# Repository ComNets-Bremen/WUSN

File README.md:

# MoleNet: A Wireless Underground Sensor Network Platform

**MoleNet** is a versatile Wireless Underground Sensor Network (WUSN) platform designed for education and low-power environmental monitoring.
This repository contains all relevant resources, including PCB layouts, source code, and examples to test and evaluate the platform.

Further information can be found on the official [MoleNet Website](https://molenet.org/)!

> ⚠️ **Note:** This is an active project. The files and directory structure are subject to change.

## New ESP32-based MoleNet!

After a long journey, we are finally at a point where we are testing the current version on a larger scale.
The latest version of MoleNet features several key improvements:

- **ESP32-S3 microcontroller**: A powerful yet energy-efficient processor that supports various development ecosystems including [MicroPython](https://micropython.org/), [Arduino](https://www.arduino.cc/), and [RiotOS](https://www.riot-os.org/)
- **SDI-12 sensor interface**: Compatible with high-quality environmental sensors
- **Micro-SD card support**: Enables extensive local data storage
- **SX1276-based LoRa transceiver**: Provides long-range wireless communication
- **On-board BME280 sensor**: Measures temperature, barometric pressure, and humidity [BME280](https://www.bosch-sensortec.com/products/environmental-sensors/humidity-sensors-bme280/)
- **Low-power design**: Ensures long battery life for extended deployments
- **qwiic connectivity**: Simplifies integration of I2C-based sensors, as, for
  example, available here: [Sparkfun](https://www.sparkfun.com/qwiic)

## Older Versions

Documentation for the ATMEGA-based MoleNet boards can be found in the [documentation directory](docs/MoleNet_ATMEGA.md).

## Changelog

The list of changes and the evolution of MoleNet is listed in the
[changelog](CHANGELOG.md).

## Publications

The following list gives some MoleNet-related publications:

- Gellhaar, M., Dede, J., Koehler, H., & Förster, A. (2016, February). Design and Evaluation of Underground Wireless Sensor Networks for Reforestation Monitoring. [In EWSN (pp. 229-230)](https://dl.acm.org/doi/10.5555/2893711.2893747).
- Zaman, I., Dede, J., Gellhaar, M., Koehler, H., & Foerster, A. (2016). Molenet: A new sensor node for underground monitoring. [IEEE SenseApp](https://www.researchgate.net/publication/309397324_MoleNet_A_New_Sensor_Node_for_Underground_Monitoring).
- Zaman, I., Gellhaar, M., Dede, J., Koehler, H., & Foerster, A. (2016, November). Design and evaluation of MoleNet for wireless underground sensor networks. In 2016 IEEE 41st conference on local computer networks workshops (LCN workshops) (pp. 145-147), [2016 IEEE 41st Conference on Local Computer Networks Workshops (LCN Workshops), Dubai, United Arab Emirates, 2016, pp. 145-147](https://doi.org/10.1109/LCN.2016.040).
- Dede, J., Helms, D., & Förster, A. (2021). MoleNet: An Underground Sensor Network for Soil Monitoring. [Electronic Communications of the EASST, 80](https://doi.org/10.14279/tuj.eceasst.80.1132)
- Sambo, D. W., Dede, J., Mitton, N., & Förster, A. (2023). FuzDeMa: A portable Fuzzy-based Decision-Making tool for reliable communication in Wireless Underground Sensor Networks. [ITU Journal on Future and Evolving Technologies, 4(3), 419-433](https://www.doi.org/10.52953/IXIP2995).

## I Want to Have MoleNet!

MoleNet is a dynamic project that is constantly evolving. At its current stage, we do not offer a ready-to-use, fully certified product with complete end-user support.

If you would like to contribute to the development of MoleNet and need hardware for testing and further development, you have two options:

1. **Build the hardware yourself.** All the necessary resources can be found in this repository.
2. **Order evaluation boards** from our partner [Intergalactic Circuits](https://intergalactic-circuits.de) for personal use.

## Contributors

Many students and researchers contribute to the MoleNet project.
See the full list of contributors in [CONTRIBUTORS.md](CONTRIBUTORS.md).

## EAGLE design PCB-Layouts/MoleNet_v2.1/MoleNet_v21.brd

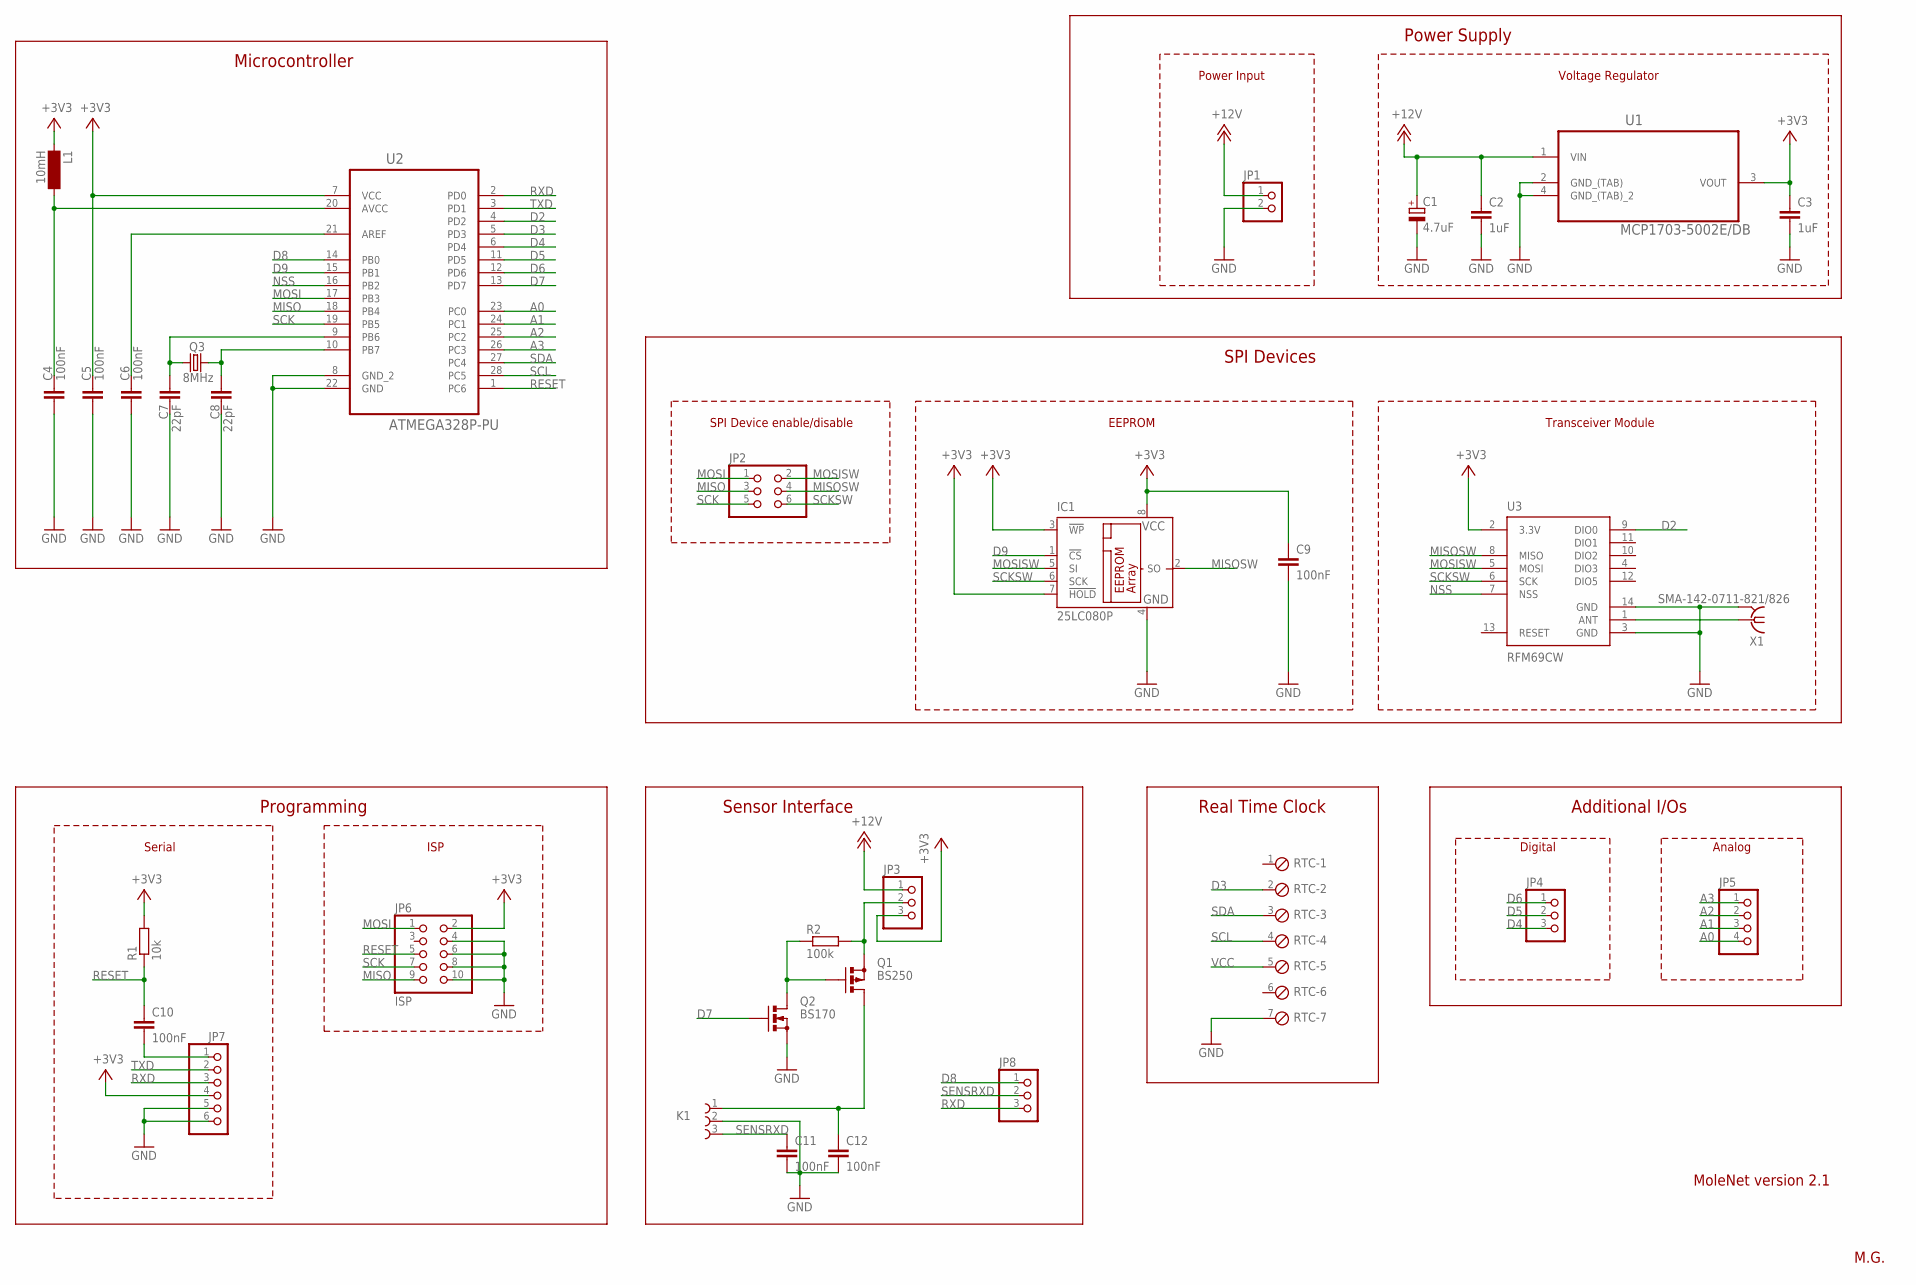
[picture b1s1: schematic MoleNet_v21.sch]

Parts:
C1: 4.7uF; E2,5-6
C2, C3: 1uF; C025-025X050
C4, C5, C6, C9, C10, C11, C12: 100nF; C025-025X050
C7, C8: 22pF; C025-025X050
IC1: 25LC080P; DIL8
JP1: PINHD-1X2; 1X02
JP2: PINHD-2X3; 2X03
JP3, JP4, JP8: PINHD-1X3; 1X03
JP5: PINHD-1X4; 1X04
JP6: ISP; 2X05
JP7: PINHD-1X6; 1X06
K1: 691241710003
L1: 10mH; BS11
Q1: BS250; SOT54E
Q2: BS170; SOT54E
Q3: 8MHz; HC18U-V
R1: 10k; 0207/10
R2: 100k; 0207/10
RTC: MPT7; 7POL254
U1: MCP1703-5002E/DB; SOT230P700X180-4N
U2: ATMEGA328P-PU; DIP254P762X457-28
U3: RFM69CW; RFM69CW-XXXS2
X1: SMA-142-0711-821/826; J502-ND-142-0711-821/826

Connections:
+12V: C1.+, C2.1, JP1.1, JP3.1, U1.1 (VIN)
A0: JP5.4, U2.23 (PC0)
A1: JP5.3, U2.24 (PC1)
A2: JP5.2, U2.25 (PC2)
A3: JP5.1, U2.26 (PC3)
D2: U2.4 (PD2), U3.9 (DIO0)
D3: RTC.2, U2.5 (PD3)
D4: JP4.3, U2.6 (PD4)
D5: JP4.2, U2.11 (PD5)
D6: JP4.1, U2.12 (PD6)
D7: Q2.G, U2.13 (PD7)
D8: JP8.1, U2.14 (PB0)
D9: IC1.1 (!CS), U2.15 (PB1)
GND: C1.-, C2.2, C3.2, C4.2, C5.2, C6.2, C7.2, C8.2, C9.2, C11.2, C12.2, IC1.4 (GND), JP1.2, JP6.4, JP6.6, JP6.8, JP6.10, JP7.5, JP7.6, K1.2, Q2.S, RTC.7, U1.2 (GND_(TAB)), U1.4 (GND_(TAB)_2), U2.8 (GND_2), U2.22 (GND), U3.3 (GND), U3.14 (GND), X1.G@1 (2), X1.G@2 (2), X1.G@3 (2), X1.G@4 (2)
MISO: JP2.3, JP6.9, U2.18 (PB4)
MISOSW: IC1.2 (SO), JP2.4, U3.8 (MISO)
MOSI: JP2.1, JP6.1, U2.17 (PB3)
MOSISW: IC1.5 (SI), JP2.2, U3.5 (MOSI)
unnamed: Q1.G, Q2.D, R2.1
unnamed: JP3.2, Q1.S, R2.2
unnamed: C7.1, Q3.1, U2.9 (PB6)
unnamed: C8.1, Q3.2, U2.10 (PB7)
unnamed: C4.1, L1.2, U2.20 (AVCC)
unnamed: C6.1, U2.21 (AREF)
unnamed: C10.2, JP7.1
unnamed: C12.1, K1.1, Q1.D
unnamed: U3.1 (ANT), X1.1
NSS: U2.16 (PB2), U3.7 (NSS)
RESET: C10.1, JP6.5, R1.1, U2.1 (PC6)
RXD: JP7.3, JP8.3, U2.2 (PD0)
SCK: JP2.5, JP6.7, U2.19 (PB5)
SCKSW: IC1.6 (SCK), JP2.6, U3.6 (SCK)
SCL: RTC.4, U2.28 (PC5)
SDA: RTC.3, U2.27 (PC4)
SENSRXD: C11.1, JP8.2, K1.3
TXD: JP7.2, U2.3 (PD1)
VCC: C3.1, C5.1, C9.1, IC1.3 (!WP), IC1.7 (!HOLD), IC1.8 (VCC), JP3.3, JP6.2, JP7.4, L1.1, R1.2, RTC.5, U1.3 (VOUT), U2.7 (VCC), U3.2 (3.3V)

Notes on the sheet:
MoleNet version 2.1
M.G.
Microcontroller
Power Supply
SPI Devices
Programming
Sensor Interface
Real Time Clock
Additional I/Os
Analog
Digital
ISP
Serial
SPI Device enable/disable
EEPROM
Transceiver Module
Power Input
Voltage Regulator

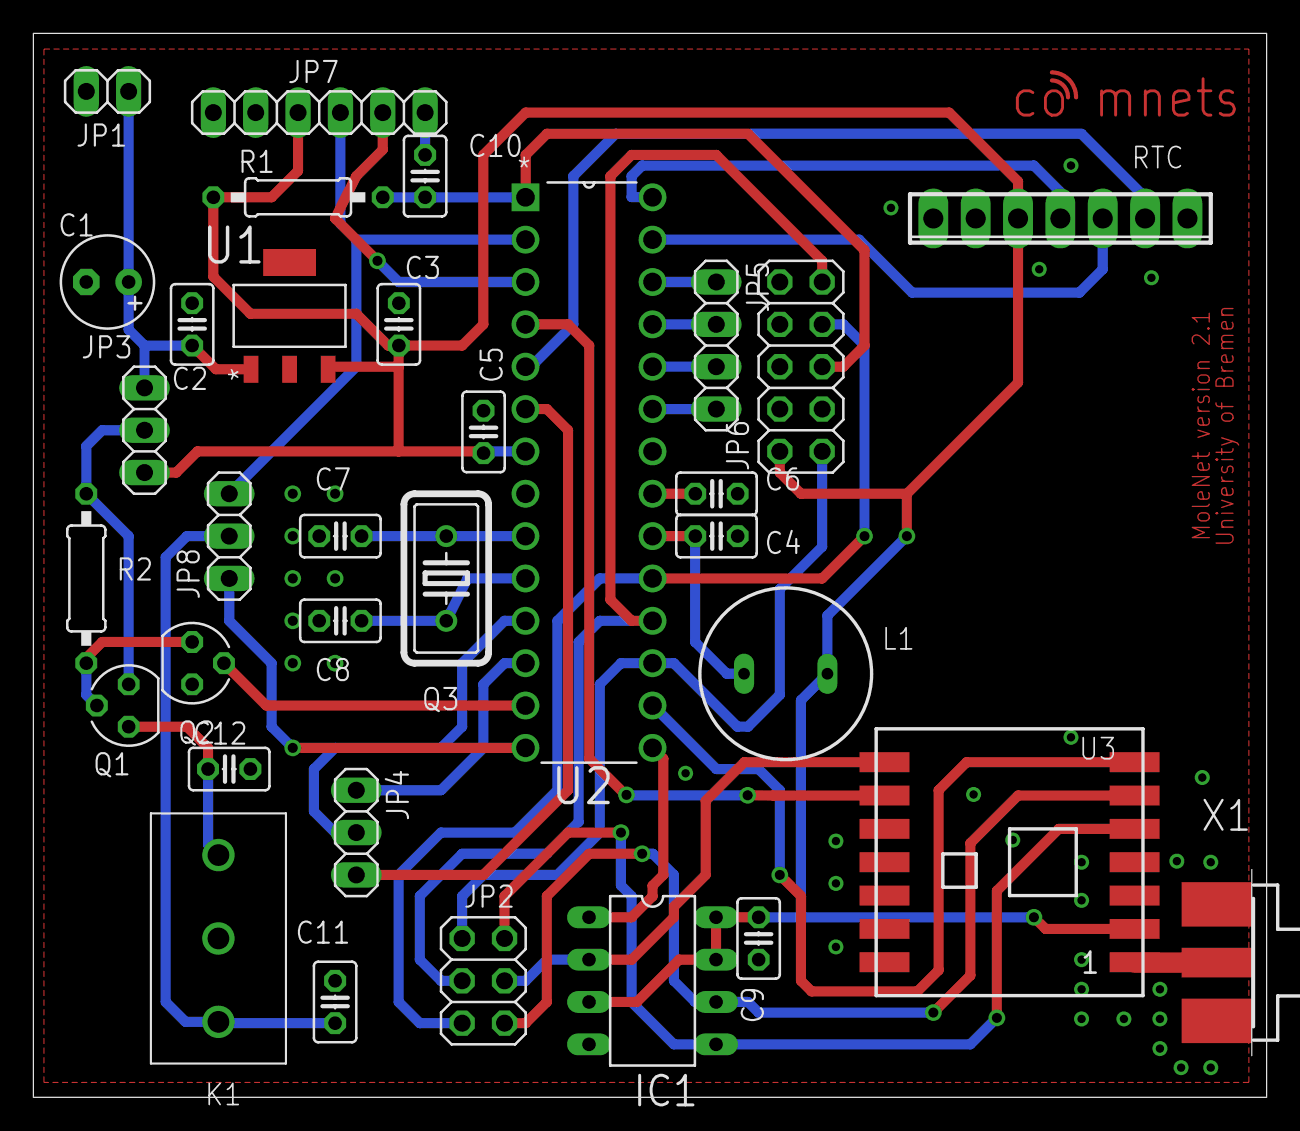
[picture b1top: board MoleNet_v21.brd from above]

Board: 2 copper layers, 74.0 x 63.8 mm, 33 parts (0 on the bottom side), 37 nets.

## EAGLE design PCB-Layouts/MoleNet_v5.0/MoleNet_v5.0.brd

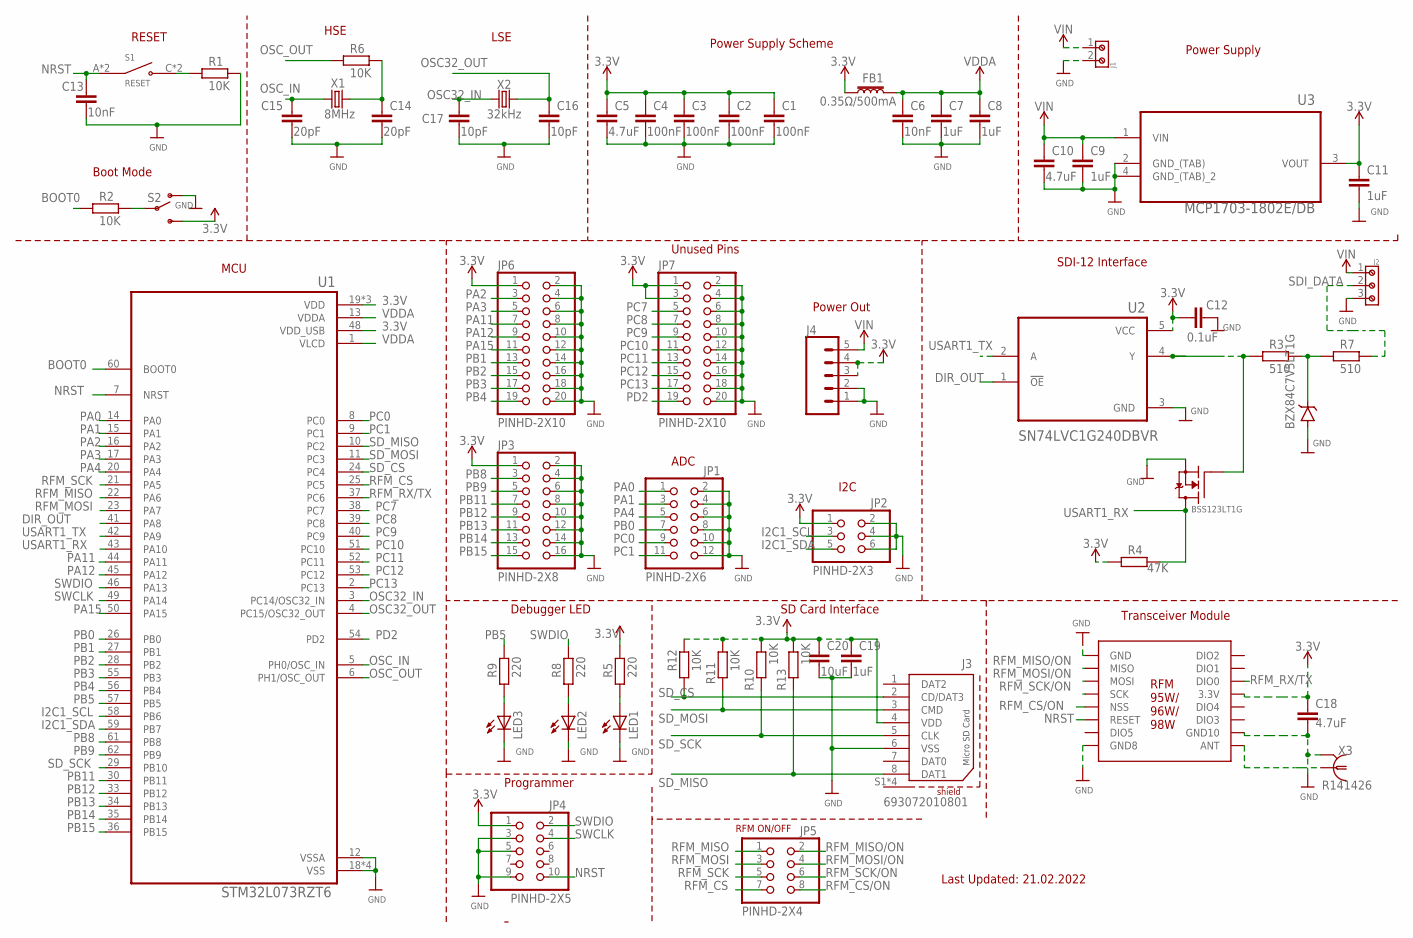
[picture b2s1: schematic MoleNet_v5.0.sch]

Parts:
C1, C2, C3, C4: 100nF; C0805
C5, C10, C18: 4.7uF; C0805
C6, C13: 10nF; C0805
C7, C8, C9, C11, C19: 1uF; C0805
C12: 0.1uF; C0805
C14, C15: 20pF; C0805
C16, C17: 10pF; C0805
C20: 10uF; C0805
FB1: 0.35Ω/500mA; 0603
J1: 691216710002
J2: 691216510003S
J3: 693072010801
J4: CONN_05; 1X05
JP1: PINHD-2X6; 2X06
JP2: PINHD-2X3; 2X03
JP3: PINHD-2X8; 2X08
JP4: PINHD-2X5; 2X05
JP5: PINHD-2X4; 2X04
JP6, JP7: PINHD-2X10; 2X10
LED1, LED2, LED3: LEDCHIPLED_0805; CHIPLED_0805
R1, R2, R6, R10, R11, R12, R13: 10K; R0805
R3, R7: 510; R0805
R4: 47K; R0805
R5, R8, R9: 220; R0805
S1: RESET; SW_TS-1187A-B-A-B
S2: SWITCH-SPDTSMD; SWITCH_SPDT_SMD
U1: STM32L073RZT6; QFP50P1200X1200X160-64N
U2: SN74LVC1G240DBVR; SOT95P280X145-5N
U3: MCP1703-1802E/DB; SOT230P700X180-4N
U$18: RFM95W/96W/98W
U$32: BSS123LT1G_STYLE-21; BZX84C7V5LT1G
U$34: BZX84C7V5LT1G_STYLE-8; BZX84C7V5LT1G
X1: 8MHz; HC49/S
X2: 32kHz; CRYSTAL-SMD-3.2X1.5MM
X3: R141426

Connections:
3.3V: C1.1, C2.1, C3.1, C4.1, C5.1, C11.1, C12.2, C18.1, C19.1, C20.1, FB1.1, J3.4 (VDD), J4.3, J4.4, JP2.1, JP3.1, JP4.1, JP6.1, JP7.1, JP7.3, R4.1, R5.2, R10.2, R11.2, R12.2, R13.2, S2.3 (S), U1.19 (VDD), U1.32 (VDD), U1.48 (VDD_USB), U1.64 (VDD), U2.5 (VCC), U3.3 (VOUT), U$18.13 (3.3V)
BOOT0: R2.1, U1.60 (BOOT0)
DIR_OUT: U1.41 (PA8), U2.1 (!OE)
GND: C1.2, C2.2, C3.2, C4.2, C5.2, C6.2, C7.2, C8.2, C9.2, C10.2, C11.2, C12.1, C13.2, C14.2, C15.2, C16.2, C17.2, C18.2, C19.2, C20.2, J1.2, J2.3, J3.6 (VSS), J4.1, J4.2, JP1.2, JP1.4, JP1.6, JP1.8, JP1.10, JP1.12, JP2.2, JP2.4, JP2.6, JP3.2, JP3.4, JP3.6, JP3.8, JP3.10, JP3.12, JP3.14, JP3.16, JP4.3, JP4.5, JP4.9, JP6.2, JP6.4, JP6.6, JP6.8, JP6.10, JP6.12, JP6.14, JP6.16, JP6.18, JP6.20, JP7.2, JP7.4, JP7.6, JP7.8, JP7.10, JP7.12, JP7.14, JP7.16, JP7.18, JP7.20, LED1.C, LED2.C, LED3.C, R1.2, S2.1 (O), U1.12 (VSSA), U1.18 (VSS), U1.31 (VSS), U1.47 (VSS), U1.63 (VSS), U2.3 (GND), U3.2 (GND_(TAB)), U3.4 (GND_(TAB)_2), U$18.1 (GND), U$18.8 (GND8), U$18.10 (GND10), U$32.P$2 (S), U$34.P$1 (A), X3.2, X3.3 (2), X3.4 (2), X3.5 (2)
I2C1_SCL: JP2.3, U1.58 (PB6)
I2C1_SDA: JP2.5, U1.59 (PB7)
unnamed: R1.1, S1.C (NO), S1.D (NO)
unnamed: R3.2, R7.1, U$34.P$3 (C)
unnamed: R3.1, U2.4 (Y), U$32.P$1 (G)
unnamed: R2.2, S2.2
unnamed: C14.1, R6.2, X1.2
unnamed: U$18.9 (ANT), X3.1
unnamed: LED1.A, R5.1
unnamed: LED2.A, R8.1
unnamed: LED3.A, R9.1
NRST: C13.1, JP4.10, S1.A (COM), S1.B (COM), U1.7 (NRST), U$18.6 (RESET)
OSC32_IN: C17.1, U1.3 (PC14/OSC32_IN), X2.P$1 (1)
OSC32_OUT: C16.1, U1.4 (PC15/OSC32_OUT), X2.P$2 (2)
OSC_IN: C15.1, U1.5 (PH0/OSC_IN), X1.1
OSC_OUT: R6.1, U1.6 (PH1/OSC_OUT)
PA0: JP1.1, U1.14 (PA0)
PA1: JP1.3, U1.15 (PA1)
PA2: JP6.3, U1.16 (PA2)
PA3: JP6.5, U1.17 (PA3)
PA4: JP1.5, U1.20 (PA4)
PA11: JP6.7, U1.44 (PA11)
PA12: JP6.9, U1.45 (PA12)
PA15: JP6.11, U1.50 (PA15)
PB0: JP1.7, U1.26 (PB0)
PB1: JP6.13, U1.27 (PB1)
PB2: JP6.15, U1.28 (PB2)
PB3: JP6.17, U1.55 (PB3)
PB4: JP6.19, U1.56 (PB4)
PB5: R9.2, U1.57 (PB5)
PB8: JP3.3, U1.61 (PB8)
PB9: JP3.5, U1.62 (PB9)
PB11: JP3.7, U1.30 (PB11)
PB12: JP3.9, U1.33 (PB12)
PB13: JP3.11, U1.34 (PB13)
PB14: JP3.13, U1.35 (PB14)
PB15: JP3.15, U1.36 (PB15)
PC0: JP1.9, U1.8 (PC0)
PC1: JP1.11, U1.9 (PC1)
PC7: JP7.5, U1.38 (PC7)
PC8: JP7.7, U1.39 (PC8)
PC9: JP7.9, U1.40 (PC9)
PC10: JP7.11, U1.51 (PC10)
PC11: JP7.13, U1.52 (PC11)
PC12: JP7.15, U1.53 (PC12)
PC13: JP7.17, U1.2 (PC13)
PD2: JP7.19, U1.54 (PD2)
RFM_CS: JP5.7, U1.25 (PC5)
RFM_CS/ON: JP5.8, U$18.5 (NSS)
RFM_MISO: JP5.1, U1.22 (PA6)
RFM_MISO/ON: JP5.2, U$18.2 (MISO)
RFM_MOSI: JP5.3, U1.23 (PA7)
RFM_MOSI/ON: JP5.4, U$18.3 (MOSI)
RFM_RX/TX: U1.37 (PC6), U$18.14 (DIO0)
RFM_SCK: JP5.5, U1.21 (PA5)
RFM_SCK/ON: JP5.6, U$18.4 (SCK)
SDI_DATA: J2.2, R7.2
SD_CS: J3.2 (CD/DAT3), R12.1, U1.24 (PC4)
SD_MISO: J3.8 (DAT1), R13.1, U1.10 (PC2)
SD_MOSI: J3.3 (CMD), R11.1, U1.11 (PC3)
SD_SCK: J3.5 (CLK), R10.1, U1.29 (PB10)
SWCLK: JP4.4, U1.49 (PA14)
SWDIO: JP4.2, R8.2, U1.46 (PA13)
USART1_RX: R4.2, U1.43 (PA10), U$32.P$3 (D)
USART1_TX: U1.42 (PA9), U2.2 (A)
VDDA: C6.1, C7.1, C8.1, FB1.2, U1.1 (VLCD), U1.13 (VDDA)
VIN: C9.1, C10.1, J1.1, J2.1, J4.5, U3.1 (VIN)

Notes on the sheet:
Last Updated: 21.02.2022
RFM ON/OFF
SDI-12 Interface
MCU
Power Supply
HSE
LSE
Boot Mode
RESET
Power Supply Scheme
Transceiver Module
Programmer
SD Card Interface
ADC
I2C
Power Out
Unused Pins
Debugger LED

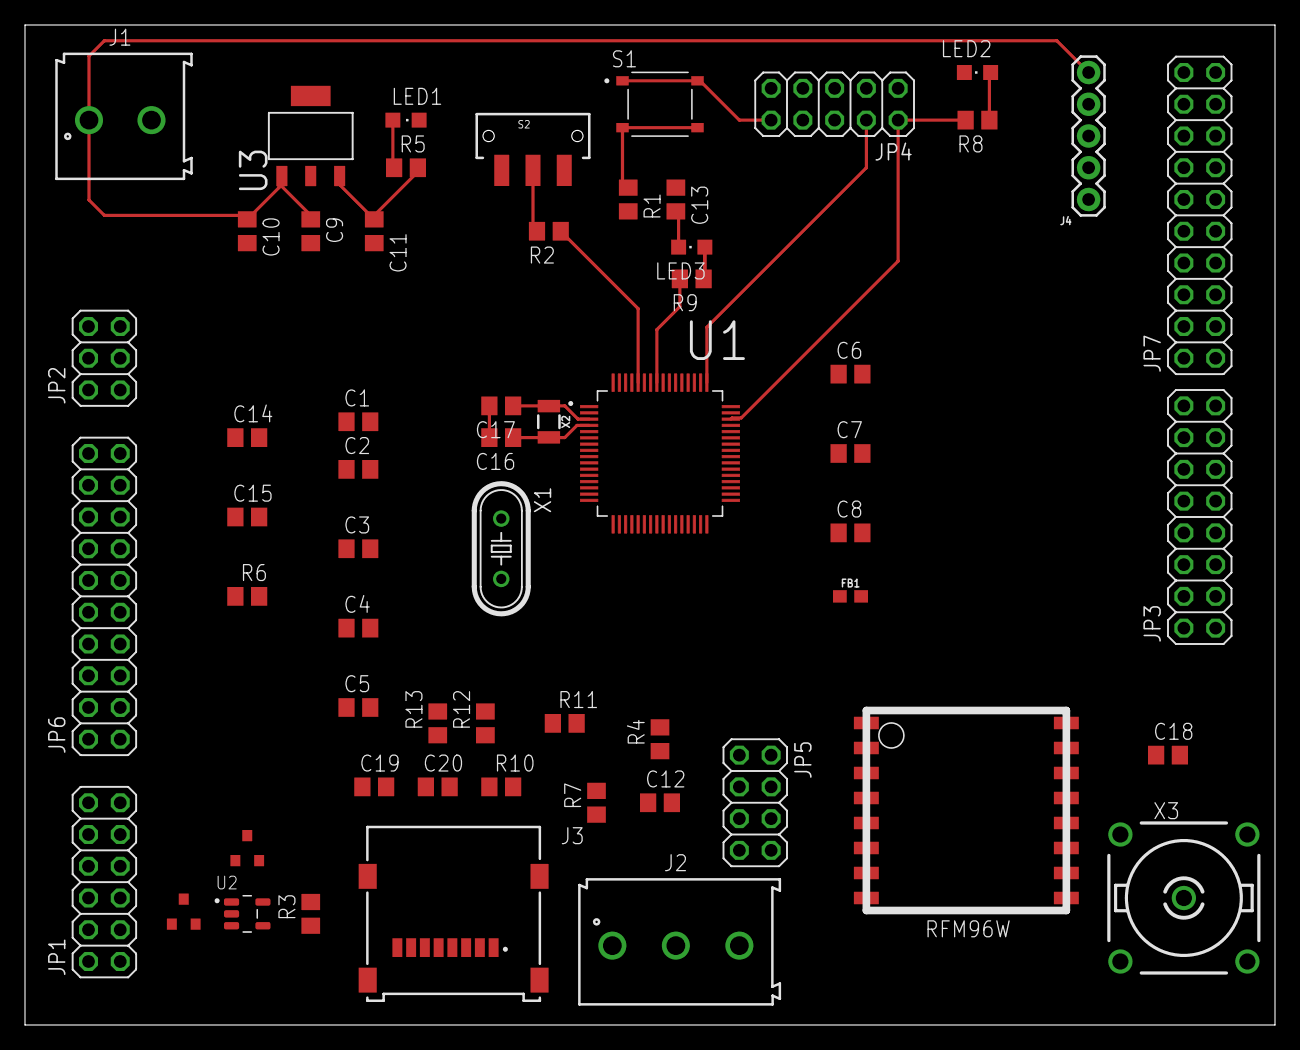
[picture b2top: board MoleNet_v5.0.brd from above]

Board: 2 copper layers, 100.0 x 80.0 mm, 59 parts (0 on the bottom side), 71 nets.

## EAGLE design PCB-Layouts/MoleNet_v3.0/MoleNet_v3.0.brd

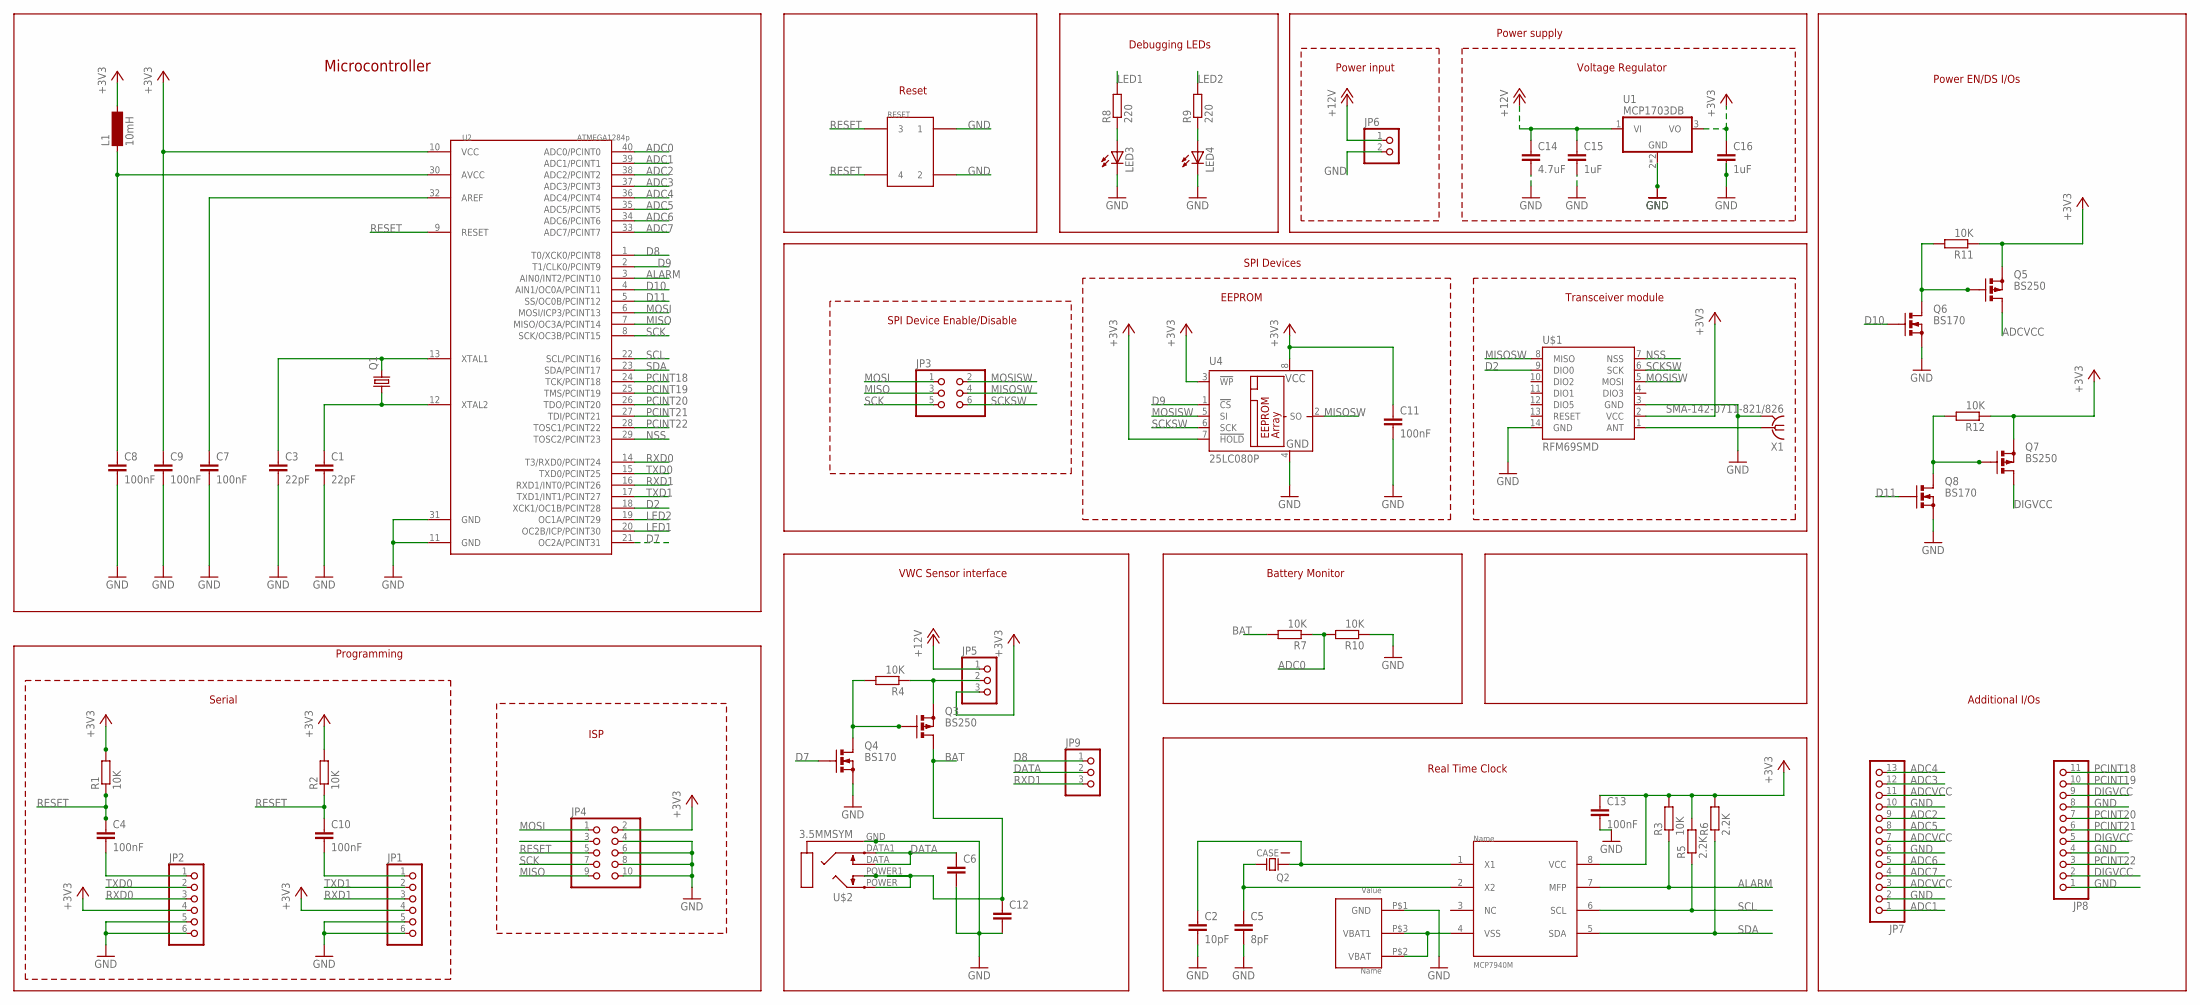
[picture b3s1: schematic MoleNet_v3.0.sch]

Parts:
C1, C3: 22pF; C025-025X050
C2: 10pF; C025-025X050
C4, C7, C8, C9, C10, C11, C13: 100nF; C025-025X050
C5: 8pF; C025-025X050
C6, C12: C-EU025-025X050; C025-025X050
C14: 4.7uF; C025-025X050
C15, C16: 1uF; C025-025X050
JP1, JP2: PINHD-1X6; 1X06
JP3: PINHD-2X3; 2X03
JP4: PINHD-2X5; 2X05
JP5, JP9: PINHD-1X3; 1X03
JP6: PINHD-1X2; 1X02
JP7: PINHD-1X13; 1X13
JP8: PINHD-1X11; 1X11
L1: 10mH; BS11
LED3, LED4: LEDLD260; LD260
Q1: CRYSTALHC18U-V; HC18U-V
Q2: MS1V-T1K-32.768KHZ/12.5PF/20PPM/TA/QC; MS1V-T1K
Q3, Q5, Q7: BS250; SOT54E
Q4, Q6, Q8: BS170; SOT54E
R1, R2, R3, R4, R7, R10, R11, R12: 10K; 0207/10
R5, R6: 2.2K; 0207/10
R8, R9: 220; 0207/10
RESET: RESDEV; PDIP-4
U1: MCP1703DB; SOT223
U2: ATMEGA1284p; DIL40
U4: 25LC080P; DIL8
U5: MCP7940M; DIP8
U7: BATHOLDER; BATDIP
U$1: RFM69SMD; RFM69
U$2: 3.5MMSYM; PDIP5
X1: SMA-142-0711-821/826; J502-ND-142-0711-821/826

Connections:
+3V3: C9.1, C11.1, C13.1, C16.1, JP1.4, JP2.4, JP4.2, JP5.3, L1.2, Q5.S, Q7.S, R1.2, R2.2, R3.2, R5.2, R6.2, R11.1, R12.1, U1.3 (VO), U2.10 (VCC), U4.3 (!WP), U4.7 (!HOLD), U4.8 (VCC), U5.8 (VCC), U$1.2 (VCC)
+12V: C14.1, C15.1, JP5.1, JP6.1, U1.1 (VI)
ADC0: R7.1, R10.2, U2.40 (ADC0/PCINT0)
ADC1: JP7.1, U2.39 (ADC1/PCINT1)
ADC2: JP7.9, U2.38 (ADC2/PCINT2)
ADC3: JP7.12, U2.37 (ADC3/PCINT3)
ADC4: JP7.13, U2.36 (ADC4/PCINT4)
ADC5: JP7.8, U2.35 (ADC5/PCINT5)
ADC6: JP7.5, U2.34 (ADC6/PCINT6)
ADC7: JP7.4, U2.33 (ADC7/PCINT7)
ADCVCC: JP7.3, JP7.7, JP7.11, Q5.D
ALARM: R3.1, U2.3 (AIN0/INT2/PCINT10), U5.7 (MFP)
BAT: C12.1, JP5.2, Q3.D, Q3.S, R4.1, R7.2, U$2.POWER, U$2.POWER1
D2: U2.18 (XCK1/OC1B/PCINT28), U$1.9 (DIO0)
D7: Q4.G, U2.21 (OC2A/PCINT31)
D8: JP9.1, U2.1 (T0/XCK0/PCINT8)
D9: U2.2 (T1/CLK0/PCINT9), U4.1 (!CS)
D10: Q6.G, U2.4 (AIN1/OC0A/PCINT11)
D11: Q8.G, U2.5 (SS/OC0B/PCINT12)
DATA: C6.1, JP9.2, U$2.DATA, U$2.DATA1
DIGVCC: JP8.2, JP8.5, JP8.9, Q7.D
GND: C1.2, C2.2, C3.2, C5.2, C6.2, C7.2, C8.2, C9.2, C11.2, C12.2, C13.2, C14.2, C15.2, C16.2, JP1.5, JP1.6, JP2.5, JP2.6, JP4.4, JP4.6, JP4.8, JP4.10, JP6.2, JP7.2, JP7.6, JP7.10, JP8.1, JP8.4, JP8.8, LED3.K (C), LED4.K (C), Q4.S, Q6.S, Q8.S, R10.1, RESET.1, RESET.2, U1.2 (GND), U1.4 (GND), U2.11 (GND), U2.31 (GND), U4.4 (GND), U7.P$1 (GND), U$1.3 (GND), U$1.14 (GND), U$2.GND, X1.G@1 (2), X1.G@2 (2), X1.G@3 (2), X1.G@4 (2)
LED1: R8.2, U2.20 (OC2B/ICP/PCINT30)
LED2: R9.2, U2.19 (OC1A/PCINT29)
MISO: JP3.3, JP4.9, U2.7 (MISO/OC3A/PCINT14)
MISOSW: JP3.4, U4.2 (SO), U$1.8 (MISO)
MOSI: JP3.1, JP4.1, U2.6 (MOSI/ICP3/PCINT13)
MOSISW: JP3.2, U4.5 (SI), U$1.5 (MOSI)
unnamed: C3.1, Q1.2, U2.13 (XTAL1)
unnamed: C1.1, Q1.1, U2.12 (XTAL2)
unnamed: C2.1, Q2.1, U5.1 (X1)
unnamed: C5.1, Q2.2, U5.2 (X2)
unnamed: C7.1, U2.32 (AREF)
unnamed: C4.2, JP2.1
unnamed: C8.1, L1.1, U2.30 (AVCC)
unnamed: C10.2, JP1.1
unnamed: U$1.1 (ANT), X1.1
unnamed: Q5.G, Q6.D, R11.2
unnamed: LED3.A, R8.1
unnamed: Q3.G, Q4.D, R4.2
unnamed: LED4.A, R9.1
unnamed: U5.4 (VSS), U7.P$2 (VBAT), U7.P$3 (VBAT1)
unnamed: Q7.G, Q8.D, R12.2
NSS: U2.29 (TOSC2/PCINT23), U$1.7 (NSS)
PCINT18: JP8.11, U2.24 (TCK/PCINT18)
PCINT19: JP8.10, U2.25 (TMS/PCINT19)
PCINT20: JP8.7, U2.26 (TDO/PCINT20)
PCINT21: JP8.6, U2.27 (TDI/PCINT21)
PCINT22: JP8.3, U2.28 (TOSC1/PCINT22)
RESET: C4.1, C10.1, JP4.5, R1.1, R2.1, RESET.3, RESET.4, U2.9 (RESET), U$1.13 (RESET)
RXD0: JP2.3, U2.14 (T3/RXD0/PCINT24)
RXD1: JP1.3, JP9.3, U2.16 (RXD1/INT0/PCINT26)
SCK: JP3.5, JP4.7, U2.8 (SCK/OC3B/PCINT15)
SCKSW: JP3.6, U4.6 (SCK), U$1.6 (SCK)
SCL: R5.1, U2.22 (SCL/PCINT16), U5.6 (SCL)
SDA: R6.1, U2.23 (SDA/PCINT17), U5.5 (SDA)
TXD0: JP2.2, U2.15 (TXD0/PCINT25)
TXD1: JP1.2, U2.17 (TXD1/INT1/PCINT27)

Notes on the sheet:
Microcontroller
Programming
Serial
ISP
VWC Sensor interface
Real Time Clock
SPI Device Enable/Disable
EEPROM
Transceiver module
SPI Devices
Voltage Regulator
Power input
Power supply
Reset
Debugging LEDs
Battery Monitor
Additional I/Os
Power EN/DS I/Os

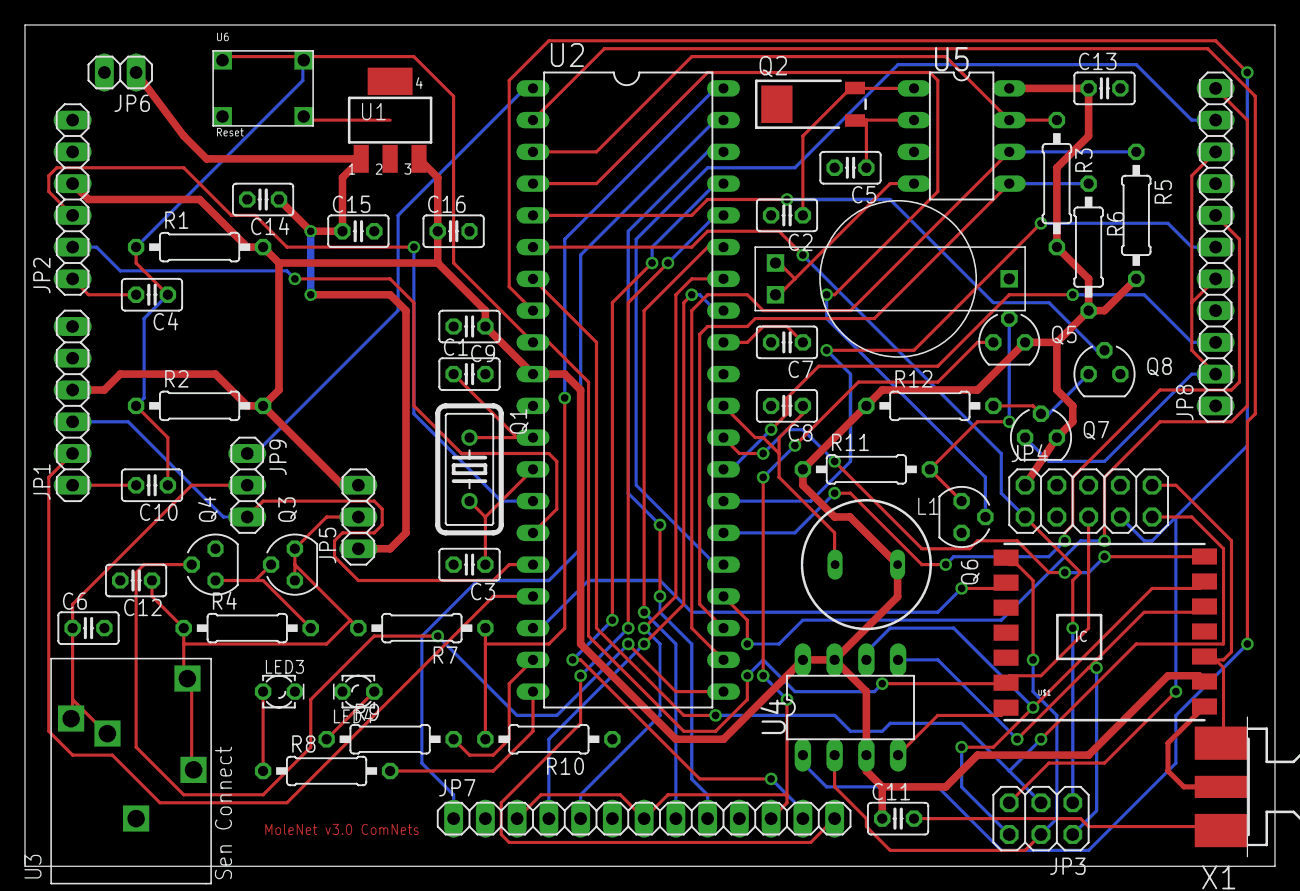
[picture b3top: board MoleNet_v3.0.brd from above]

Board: 2 copper layers, 100.0 x 67.3 mm, 57 parts (0 on the bottom side), 58 nets.

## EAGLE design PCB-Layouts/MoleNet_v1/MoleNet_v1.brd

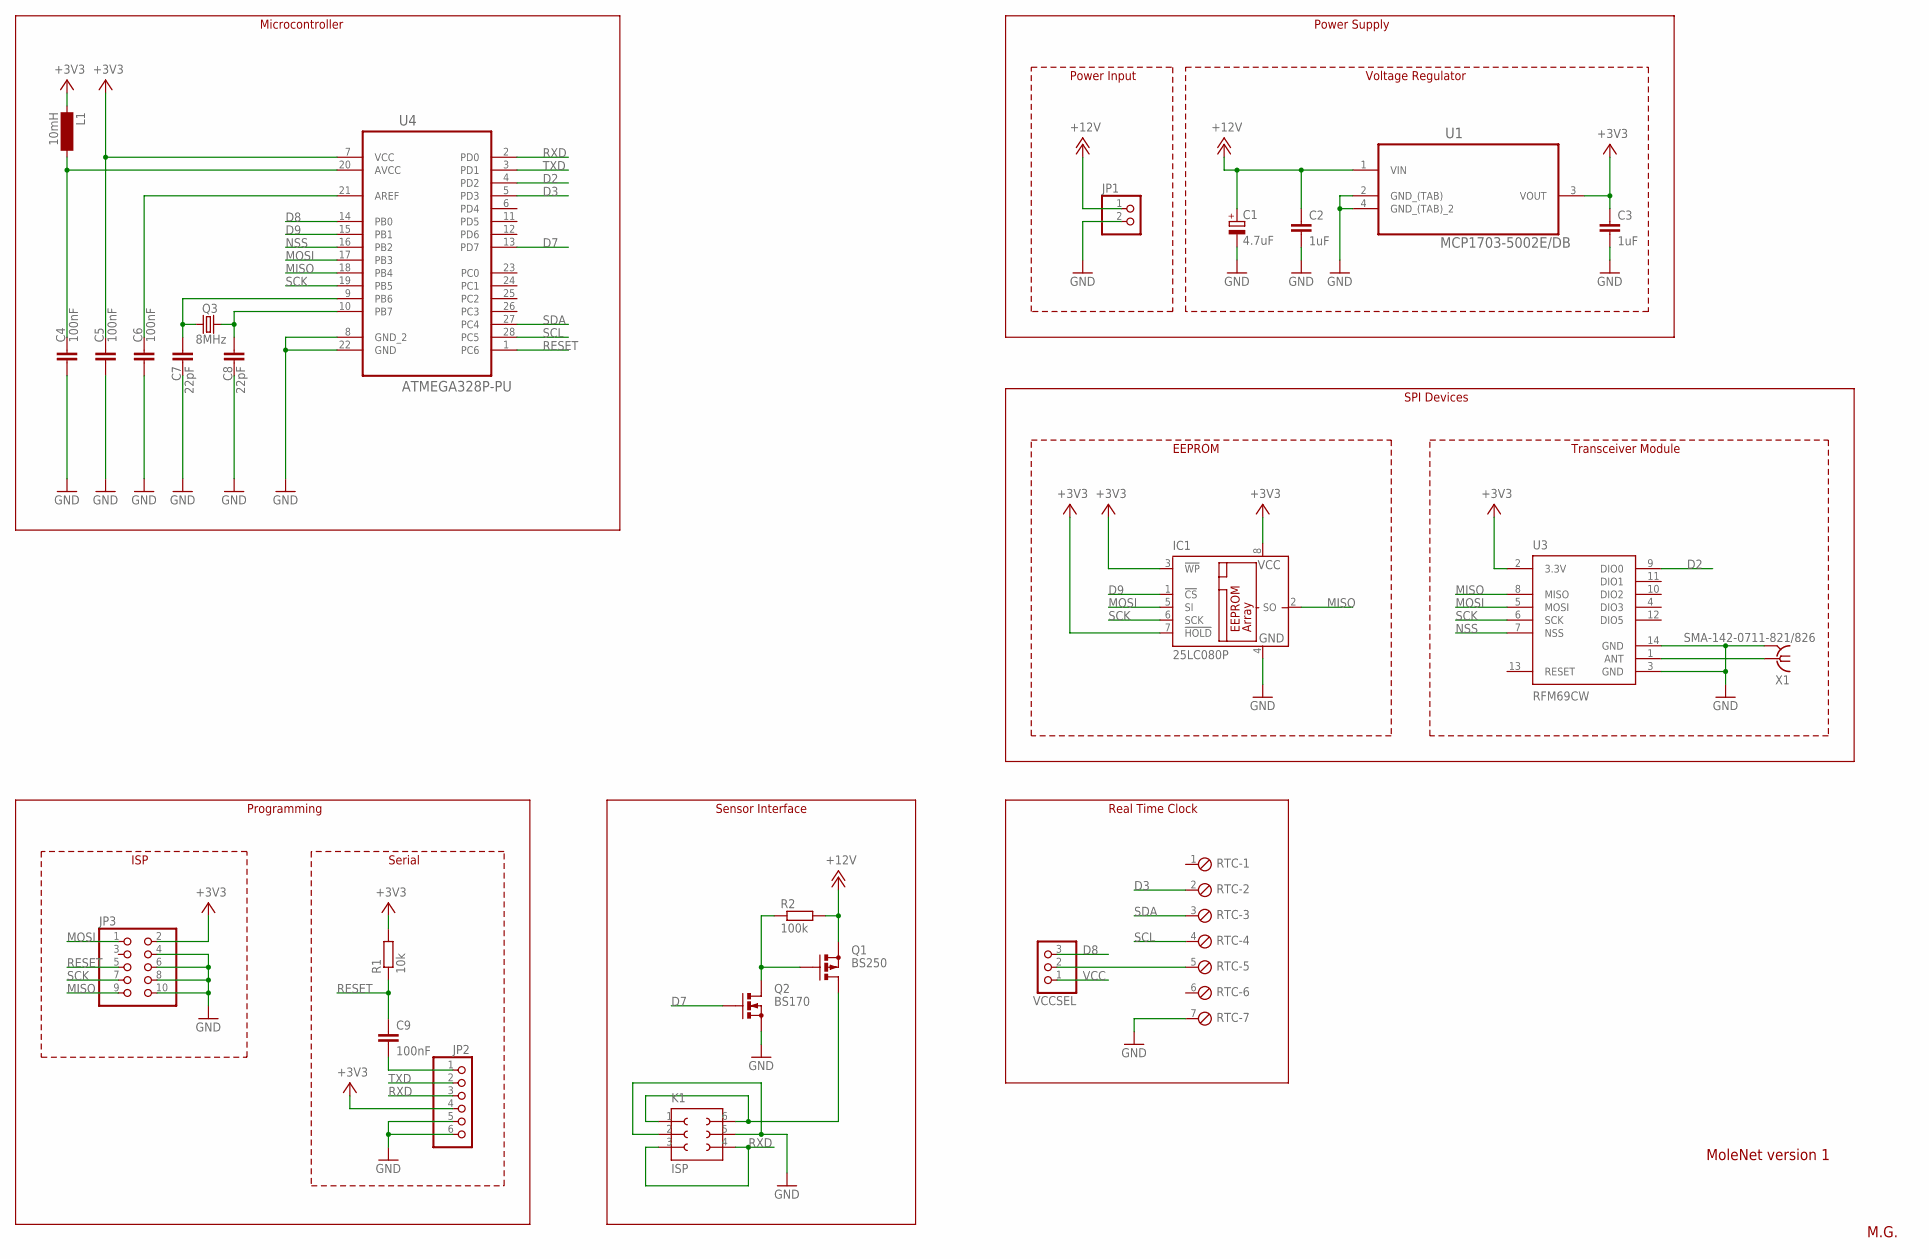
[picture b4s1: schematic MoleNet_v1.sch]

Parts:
C1: 4.7uF; E2,5-6
C2, C3: 1uF; C025-025X050
C4, C5, C6, C9: 100nF; C025-025X050
C7, C8: 22pF; C025-025X050
IC1: 25LC080P; DIL8
JP1: PINHD-1X2; 1X02
JP2: PINHD-1X6; 1X06
JP3: PINHD-2X5; 2X05
K1: ISP; 691411710003
L1: 10mH; BS11
Q1: BS250; SOT54E
Q2: BS170; SOT54E
Q3: 8MHz; HC18U-V
R1: 10k; 0207/10
R2: 100k; 0207/10
RTC: MPT7; 7POL254
U1: MCP1703-5002E/DB; SOT230P700X180-4N
U3: RFM69CW; RFM69CW-XXXS2
U4: ATMEGA328P-PU; DIP254P762X457-28
VCCSEL: PINHD-1X3; 1X03
X1: SMA-142-0711-821/826; J502-ND-142-0711-821/826

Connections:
+12V: C1.+, C2.1, JP1.1, Q1.S, R2.2, U1.1 (VIN)
D2: U3.9 (DIO0), U4.4 (PD2)
D3: RTC.2, U4.5 (PD3)
D7: Q2.G, U4.13 (PD7)
D8: U4.14 (PB0), VCCSEL.3
D9: IC1.1 (!CS), U4.15 (PB1)
GND: C1.-, C2.2, C3.2, C4.2, C5.2, C6.2, C7.2, C8.2, IC1.4 (GND), JP1.2, JP2.5, JP2.6, JP3.4, JP3.6, JP3.8, JP3.10, K1.2, K1.5, Q2.S, RTC.7, U1.2 (GND_(TAB)), U1.4 (GND_(TAB)_2), U3.3 (GND), U3.14 (GND), U4.8 (GND_2), U4.22 (GND), X1.G@1 (2), X1.G@2 (2), X1.G@3 (2), X1.G@4 (2)
MISO: IC1.2 (SO), JP3.9, U3.8 (MISO), U4.18 (PB4)
MOSI: IC1.5 (SI), JP3.1, U3.5 (MOSI), U4.17 (PB3)
unnamed: Q1.G, Q2.D, R2.1
unnamed: K1.1, K1.6, Q1.D
unnamed: C7.1, Q3.1, U4.9 (PB6)
unnamed: C8.1, Q3.2, U4.10 (PB7)
unnamed: C4.1, L1.2, U4.20 (AVCC)
unnamed: C6.1, U4.21 (AREF)
unnamed: C9.2, JP2.1
unnamed: RTC.5, VCCSEL.2
unnamed: U3.1 (ANT), X1.1
NSS: U3.7 (NSS), U4.16 (PB2)
RESET: C9.1, JP3.5, R1.1, U4.1 (PC6)
RXD: JP2.3, K1.3, K1.4, U4.2 (PD0)
SCK: IC1.6 (SCK), JP3.7, U3.6 (SCK), U4.19 (PB5)
SCL: RTC.4, U4.28 (PC5)
SDA: RTC.3, U4.27 (PC4)
TXD: JP2.2, U4.3 (PD1)
VCC: C3.1, C5.1, IC1.3 (!WP), IC1.7 (!HOLD), IC1.8 (VCC), JP2.4, JP3.2, L1.1, R1.2, U1.3 (VOUT), U3.2 (3.3V), U4.7 (VCC), VCCSEL.1

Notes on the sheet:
MoleNet version 1
M.G.
Microcontroller
Power Supply
SPI Devices
Real Time Clock
Sensor Interface
Programming
ISP
Serial
EEPROM
Transceiver Module
Power Input
Voltage Regulator

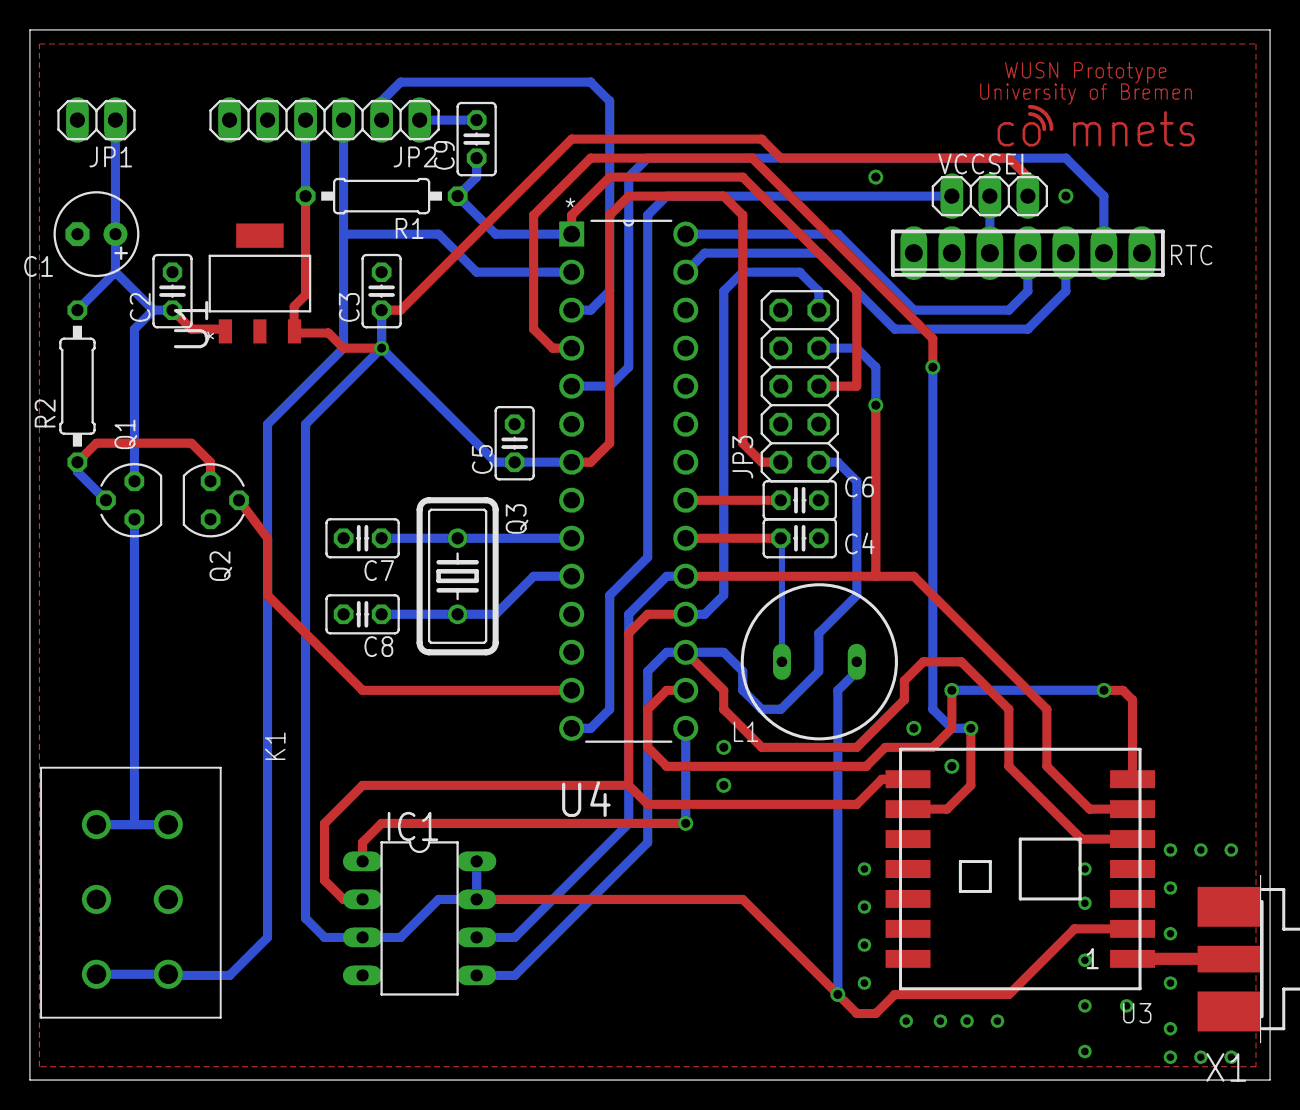
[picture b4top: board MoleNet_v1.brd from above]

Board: 2 copper layers, 82.9 x 70.2 mm, 26 parts (0 on the bottom side), 26 nets.

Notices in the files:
parts and their libraries:
SparkFun-RF: Licensing: Creative Commons ShareAlike 4.0 International - https://creativecommons.org/licenses/by-sa/4.0
Terminal_Blocks_Connectors_rev15e: Copyright: Würth Elektronik
